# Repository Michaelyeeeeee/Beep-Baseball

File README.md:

baseball.kicad_sch and baseball.kicad_pcb are final products

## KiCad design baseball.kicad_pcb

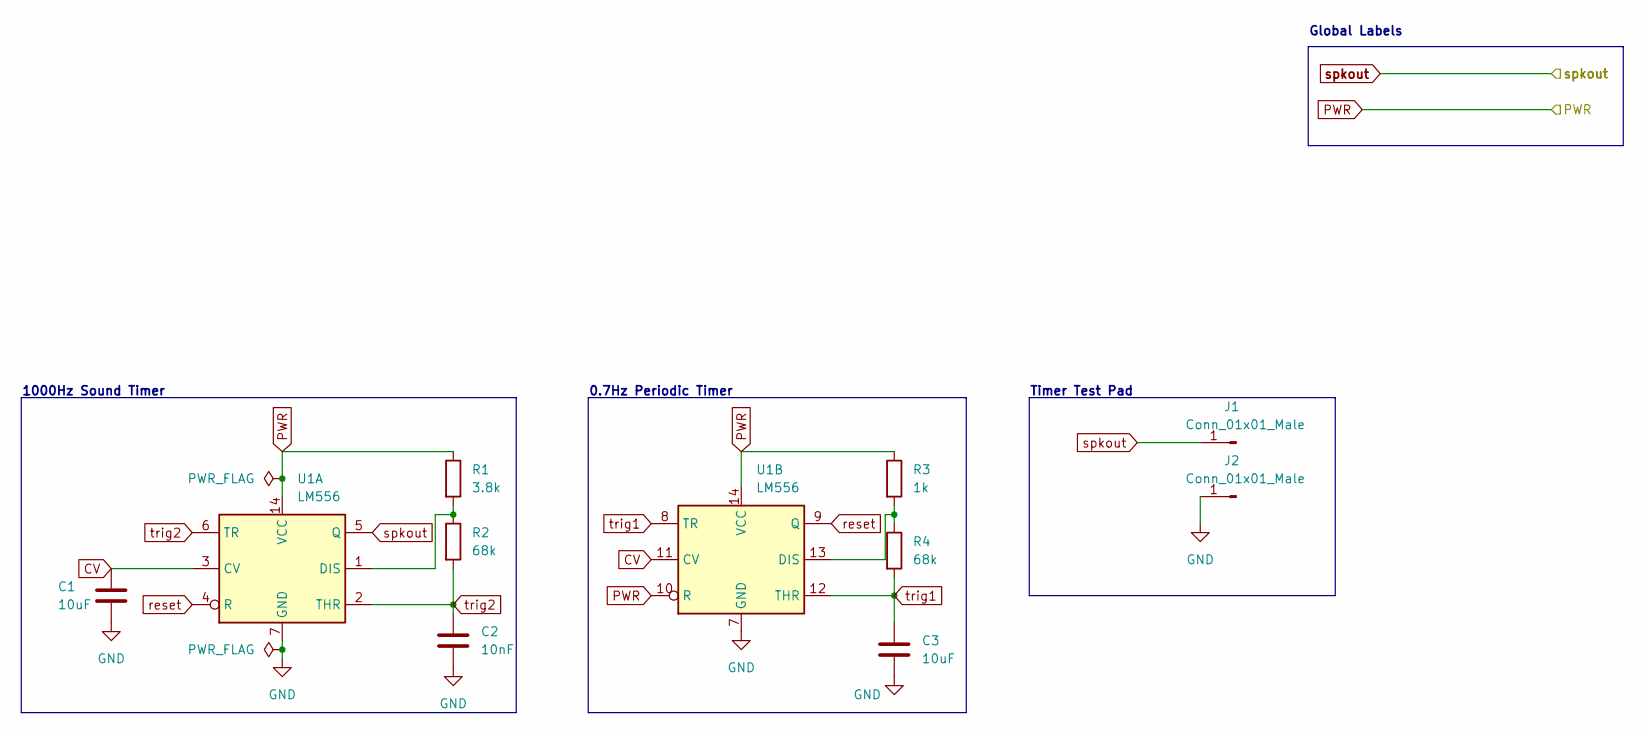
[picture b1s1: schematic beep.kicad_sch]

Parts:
C1, C3: 10uF; C_0402_1005Metric
C2: 10nF; C_0402_1005Metric
J1, J2: Conn_01x01_Male; TestPoint_Pad_D2.0mm
R1: 3.8k; R_0402_1005Metric
R2, R4: 68k; R_0402_1005Metric
R3: 1k; R_0402_1005Metric
U1: LM556; 556

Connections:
CV: C1.1, U1.3 (CV), U1.11 (CV)
GND: C1.2, C2.2, C3.2, J2.1, U1.7 (GND); also elsewhere on the board
unnamed: R1.2, R2.1, U1.1 (DIS)
unnamed: R3.2, R4.1, U1.13 (DIS)
PWR: R1.1, R3.1, U1.10 (R), U1.14 (VCC); also elsewhere on the board
reset: U1.4 (R), U1.9 (Q)
spkout: J1.1, U1.5 (Q); also elsewhere on the board
trig1: C3.1, R4.2, U1.8 (TR), U1.12 (THR)
trig2: C2.1, R2.2, U1.2 (THR), U1.6 (TR)

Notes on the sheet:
Global Labels
1000Hz Sound Timer
0.7Hz Periodic Timer
Timer Test Pad

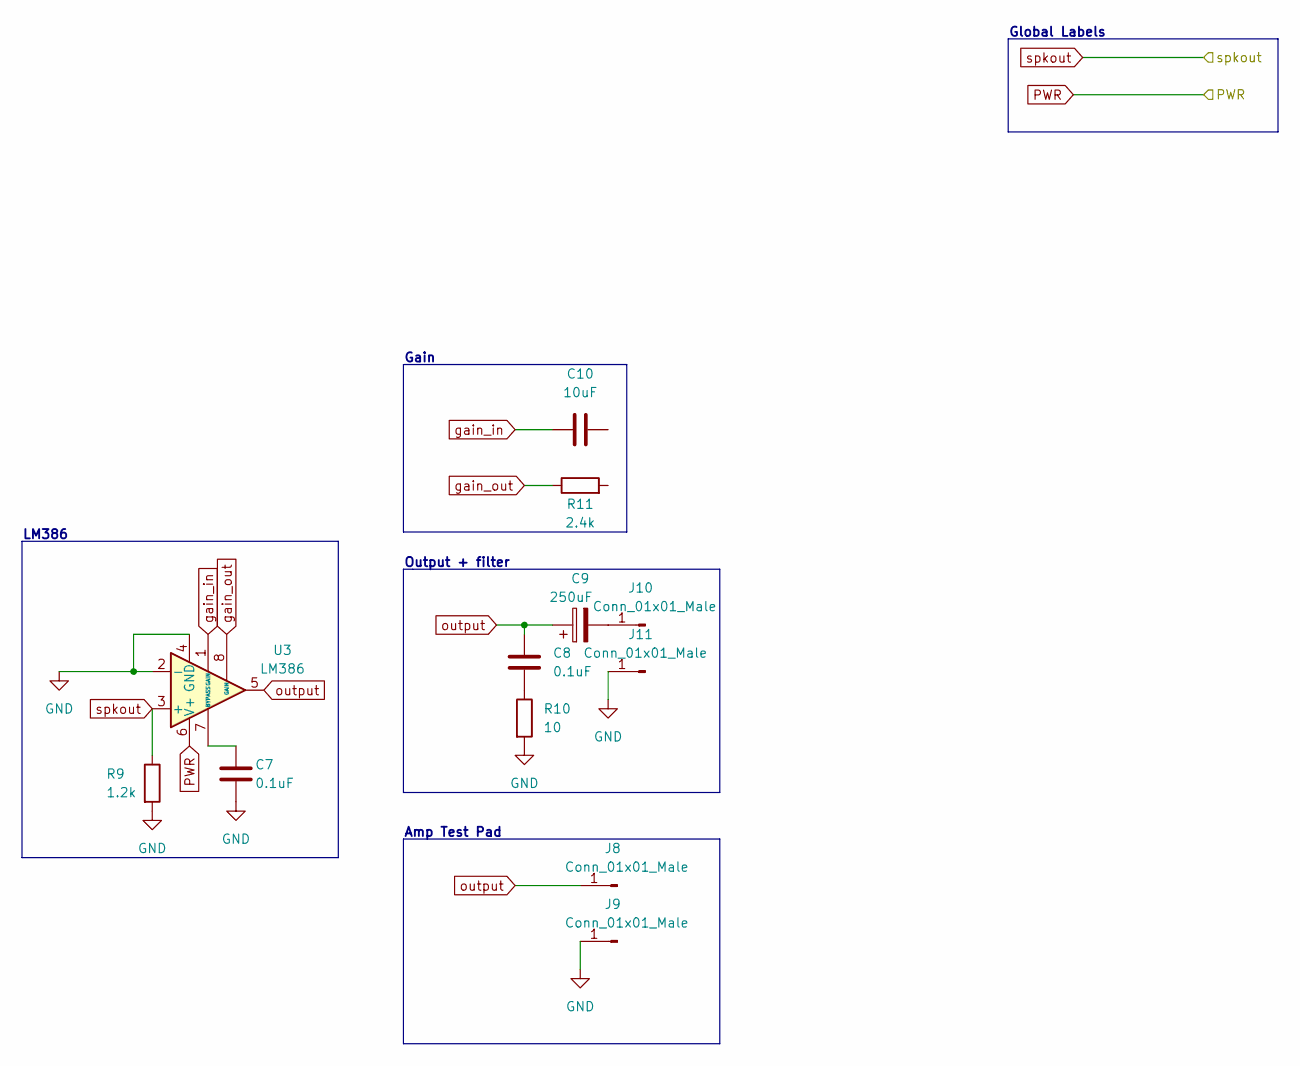
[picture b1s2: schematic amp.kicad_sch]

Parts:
C7, C8: 0.1uF; C_0402_1005Metric
C9: 250uF; CP_Elec_6.3x7.7
C10: 10uF; C_0402_1005Metric
J8, J9, J10, J11: Conn_01x01_Male; TestPoint_Pad_D2.0mm
R9: 1.2k; R_0402_1005Metric
R10: 10; R_0402_1005Metric
R11: 2.4k; R_0402_1005Metric
U3: LM386; SOIC127P600X175-8N

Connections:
GND: C7.2, J9.1, J11.1, R9.2, R10.2, U3.2 (-), U3.4 (GND); also elsewhere on the board
unnamed: C7.1, U3.7 (BYPASS)
unnamed: C8.2, R10.1
unnamed: C9.2, J10.1
PWR: U3.6 (V+); also elsewhere on the board
gain_in: C10.1, U3.1 (GAIN)
gain_out: R11.1, U3.8 (GAIN)
output: C8.1, C9.1, J8.1, U3.5
spkout: R9.1, U3.3 (+); also elsewhere on the board

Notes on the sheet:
Gain
Amp Test Pad
Global Labels
Output + filter
LM386

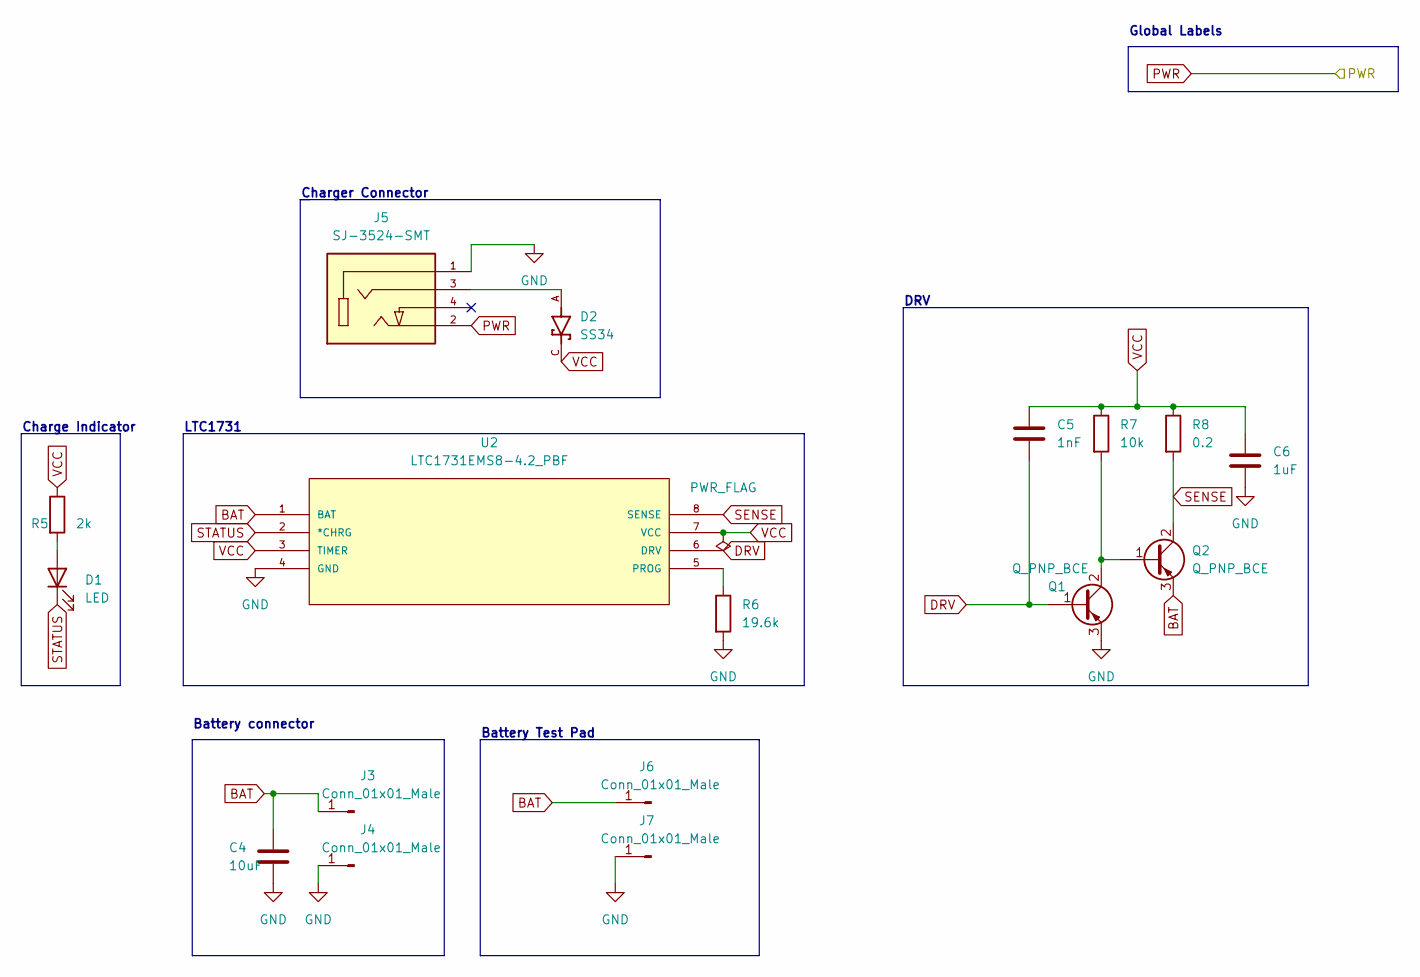
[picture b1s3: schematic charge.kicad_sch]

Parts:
C4: 10uF; C_0402_1005Metric
C5: 1nF; C_0402_1005Metric
C6: 1uF; C_0402_1005Metric
D1: LED; LED_0402_1005Metric
D2: SS34; DIOM7959X265N; PARTREV 31 Aug 2016
J3, J4, J6, J7: Conn_01x01_Male; TestPoint_Pad_D2.0mm
J5: SJ-3524-SMT; CUI_SJ-3524-SMT-GR; PARTREV 1.03
Q1, Q2: Q_PNP_BCE; TO-92
R5: 2k; R_0402_1005Metric
R6: 19.6k; R_0402_1005Metric
R7: 10k; R_0402_1005Metric
R8: 0.2; R_0402_1005Metric
U2: LTC1731EMS8-4.2_PBF; SOIC127P600X175-8N; MANUFACTURER_PART_NUMBER ltc1731ems88.4

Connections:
BAT: C4.1, J3.1, J6.1, Q2.3 (E), U2.1 (BAT)
DRV: C5.2, Q1.1 (B), U2.6 (DRV)
GND: C4.2, C6.2, J4.1, J5.1, J7.1, Q1.3 (E), R6.2, U2.4 (GND); also elsewhere on the board
unnamed: D1.2 (A), R5.2
unnamed: D2.A, J5.3
unnamed: Q1.2 (C), Q2.1 (B), R7.2
unnamed: R6.1, U2.5 (PROG)
PWR: J5.2; also elsewhere on the board
SENSE: Q2.2 (C), R8.2, U2.8 (SENSE)
STATUS: D1.1 (K), U2.2 (*CHRG)
VCC: C5.1, C6.1, D2.C, R5.1, R7.1, R8.1, U2.3 (TIMER), U2.7 (VCC)

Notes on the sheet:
Global Labels
LTC1731
DRV
Charge Indicator
Charger Connector
Battery Test Pad
Battery connector

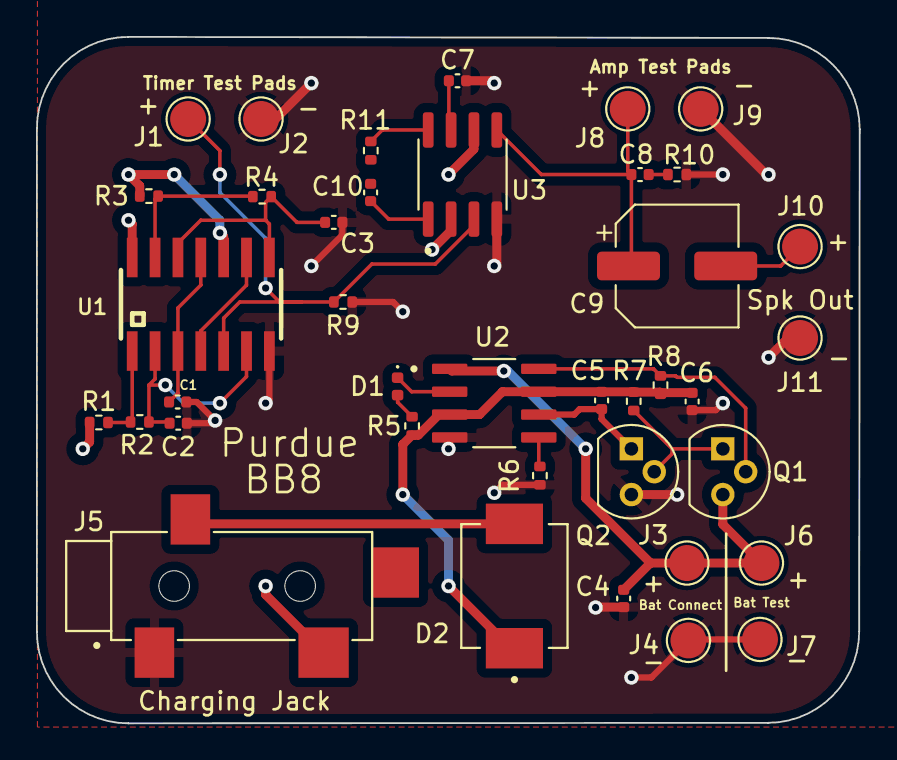
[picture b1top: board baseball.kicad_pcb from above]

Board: 2 copper layers, 45.7 x 38.1 mm, 39 parts (0 on the bottom side), 24 nets.

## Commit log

2025-10-16 Add final product information to README
